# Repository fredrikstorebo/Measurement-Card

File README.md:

# Measurement-Card
Measurment Card Designed For Measuring Voltage And Current.

Measurement card for measuring voltage and current designed in KiCad.

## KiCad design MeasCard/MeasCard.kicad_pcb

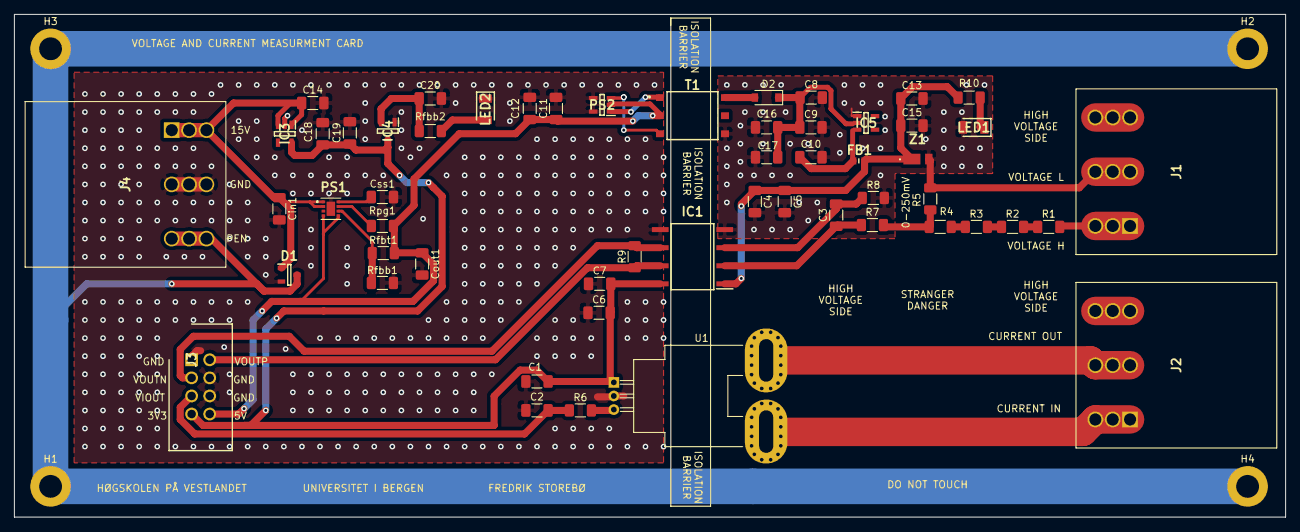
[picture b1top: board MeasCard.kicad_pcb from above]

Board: 2 copper layers, 178.6 x 70.6 mm, 59 parts (0 on the bottom side), 33 nets.

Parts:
C1, C4, C6: 0.1e-6; C_1206_3216Metric_Pad1.33x1.80mm_HandSolder
C2, C5, C7: 1e-6; C_1206_3216Metric_Pad1.33x1.80mm_HandSolder
C3: 330e-12; C_1206_3216Metric_Pad1.33x1.80mm_HandSolder
C8, C10, C11, C16: 10e-9; C_1206_3216Metric_Pad1.33x1.80mm_HandSolder
C9, C12, C13, C14, C15, C17, C18, C19, C20: 0.1e-9; C_1206_3216Metric_Pad1.33x1.80mm_HandSolder
Cin1: 10e-6; C_1206_3216Metric_Pad1.33x1.80mm_HandSolder
Cout1: 22e-6; C_1206_3216Metric_Pad1.33x1.80mm_HandSolder
Css1: 430e-12; C_1206_3216Metric_Pad1.33x1.80mm_HandSolder
D1: PESD15VL2BT,215; SOT95P230X110-3N
D2: MBR0520LT; D_SOD-123
FB1: MMZ1608B102CTA00; BEADC1608X95N
H1, H2, H3, H4: MountingHole_Pad; MountingHole_3.2mm_M3_ISO7380_Pad
IC1: AMC1100DUBR; SOP254P1040X485-8N
IC3: MIC5225-3.3YM5-TR; SOT95P280X145-5N
IC4: BD49K33G-TL; SOT95P280X125-3N
IC5: TLV70450DBVT; SOT95P280X145-5N
J1, J2, J4: 1717017
J3: 70246-0802; SHDR8W99P254_2X4_1778X889X947P
LED1: LG_L29K-G2J1-24-Z; LEDC3216X200N
LED2: APTD3216LCGCK; LEDC3216X200N
PS1: TPS82130SILT
PS2: SN6501DBVR; SOT95P280X145-5N
R1, R2, R3, R4: 59.75e3; R_1206_3216Metric_Pad1.30x1.75mm_HandSolder
R5: 1000; R_1206_3216Metric_Pad1.30x1.75mm_HandSolder
R6, R7, R8: 12; R_1206_3216Metric_Pad1.30x1.75mm_HandSolder
R9: 100; R_1206_3216Metric_Pad1.30x1.75mm_HandSolder
R10: 3.16; R_1206_3216Metric_Pad1.30x1.75mm_HandSolder
Rfbb1, Rfbb2: 100e3; R_1206_3216Metric_Pad1.30x1.75mm_HandSolder
Rfbt1: 523e3; R_1206_3216Metric_Pad1.30x1.75mm_HandSolder
Rpg1: 100e3; R_1206_3216Metric_Pad1.30x1.75mm_HandSolder
T1: 760390015
U1: ACS758xCB-050B-PFF; Allegro_CB_PFF
Z1: DFLZ6V2-7; DFLZ6V87

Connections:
3.3V: C1.1, C6.2, C7.2, C18.1, C19.1, IC1.8, IC3.5, IC4.3, J3.7, U1.1
5V: C11.2, C12.2, Cout1.1, J3.8, PS1.4, PS1.5, PS2.2, Rfbt1.2, Rpg1.2, T1.2
+5V_ISO: C4.1, C5.1, C13.1, C15.1, FB1.2, IC1.1, R10.2, Z1.1
+6V_ISO: C8.1, C9.1, C16.1, C17.1, D2.1, IC5.2
GND: C1.2, C2.2, C6.1, C7.1, C11.1, C12.1, C14.2, C18.2, C19.2, C20.2, Cin1.2, Cout1.2, Css1.2, D1.2, IC1.5, IC3.2, IC4.1, J3.1, J3.4, J3.6, J4.4, J4.5, J4.6, LED2.1, PS1.3, PS1.9, PS2.4, PS2.5, Rfbb1.1, U1.2
GNDD: C4.2, C5.2, C8.2, C9.2, C10.2, C13.2, C15.2, C16.2, C17.2, IC1.4, IC5.1, J1.4, J1.5, J1.6, LED1.2, R5.1, R8.2, T1.4, Z1.2
unnamed: C2.1, J3.5, R6.1
unnamed: C3.1, IC1.2, R7.1
unnamed: C3.2, IC1.3, R8.1
unnamed: C10.1, FB1.1, IC5.3
unnamed: C14.1, Cin1.1, D1.1, IC3.1, IC3.3, J4.1, J4.2, J4.3, PS1.1, PS1.2
unnamed: C20.1, IC4.2, Rfbb2.2
unnamed: Css1.1, PS1.8
unnamed: D1.3, H1.1, H2.1, H3.1, H4.1, J4.7, J4.8, J4.9
unnamed: D2.2, T1.6
unnamed: IC1.6, J3.3, R9.1
unnamed: IC1.7, J3.2, R9.2
unnamed: J1.1, J1.2, J1.3, R1.2
unnamed: J1.7, J1.8, J1.9
unnamed: J2.1, J2.2, J2.3, U1.4
unnamed: J2.4, J2.5, J2.6, U1.5
unnamed: J2.7, J2.8, J2.9
unnamed: LED1.1, R10.1
unnamed: LED2.2, Rfbb2.1
unnamed: PS1.6, Rfbb1.2, Rfbt1.1
unnamed: PS1.7, Rpg1.1
unnamed: PS2.1, T1.1
unnamed: PS2.3, T1.3
unnamed: R1.1, R2.2
unnamed: R2.1, R3.2
unnamed: R3.1, R4.2
unnamed: R4.1, R5.2, R7.2
unnamed: R6.2, U1.3

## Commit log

2021-05-30 added files
